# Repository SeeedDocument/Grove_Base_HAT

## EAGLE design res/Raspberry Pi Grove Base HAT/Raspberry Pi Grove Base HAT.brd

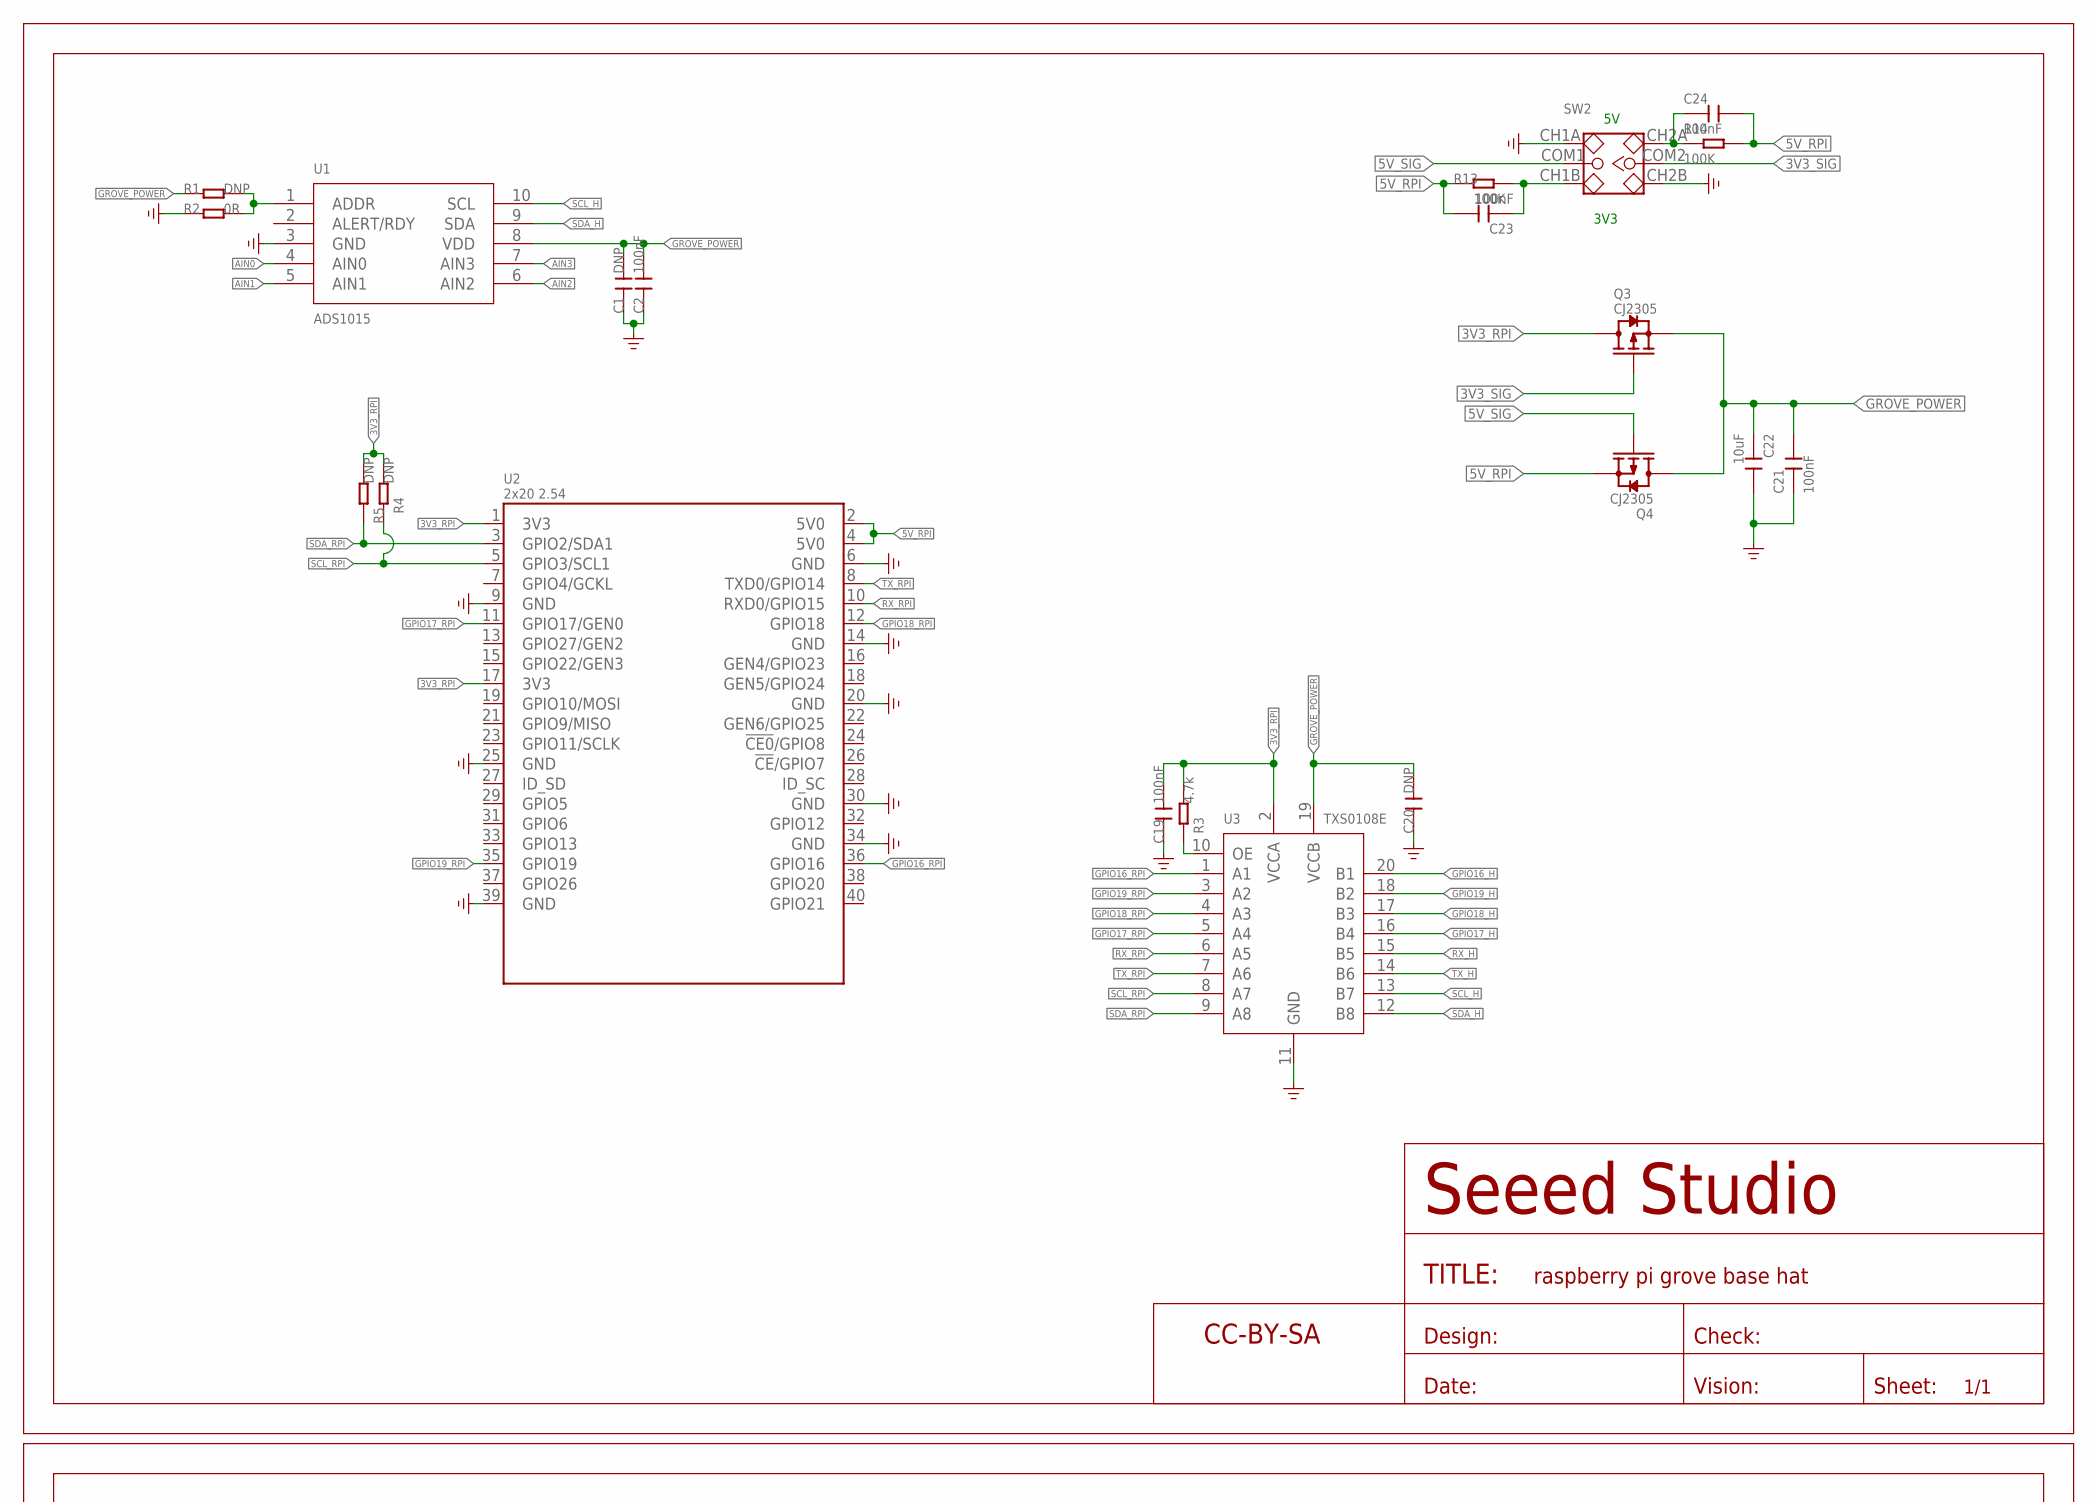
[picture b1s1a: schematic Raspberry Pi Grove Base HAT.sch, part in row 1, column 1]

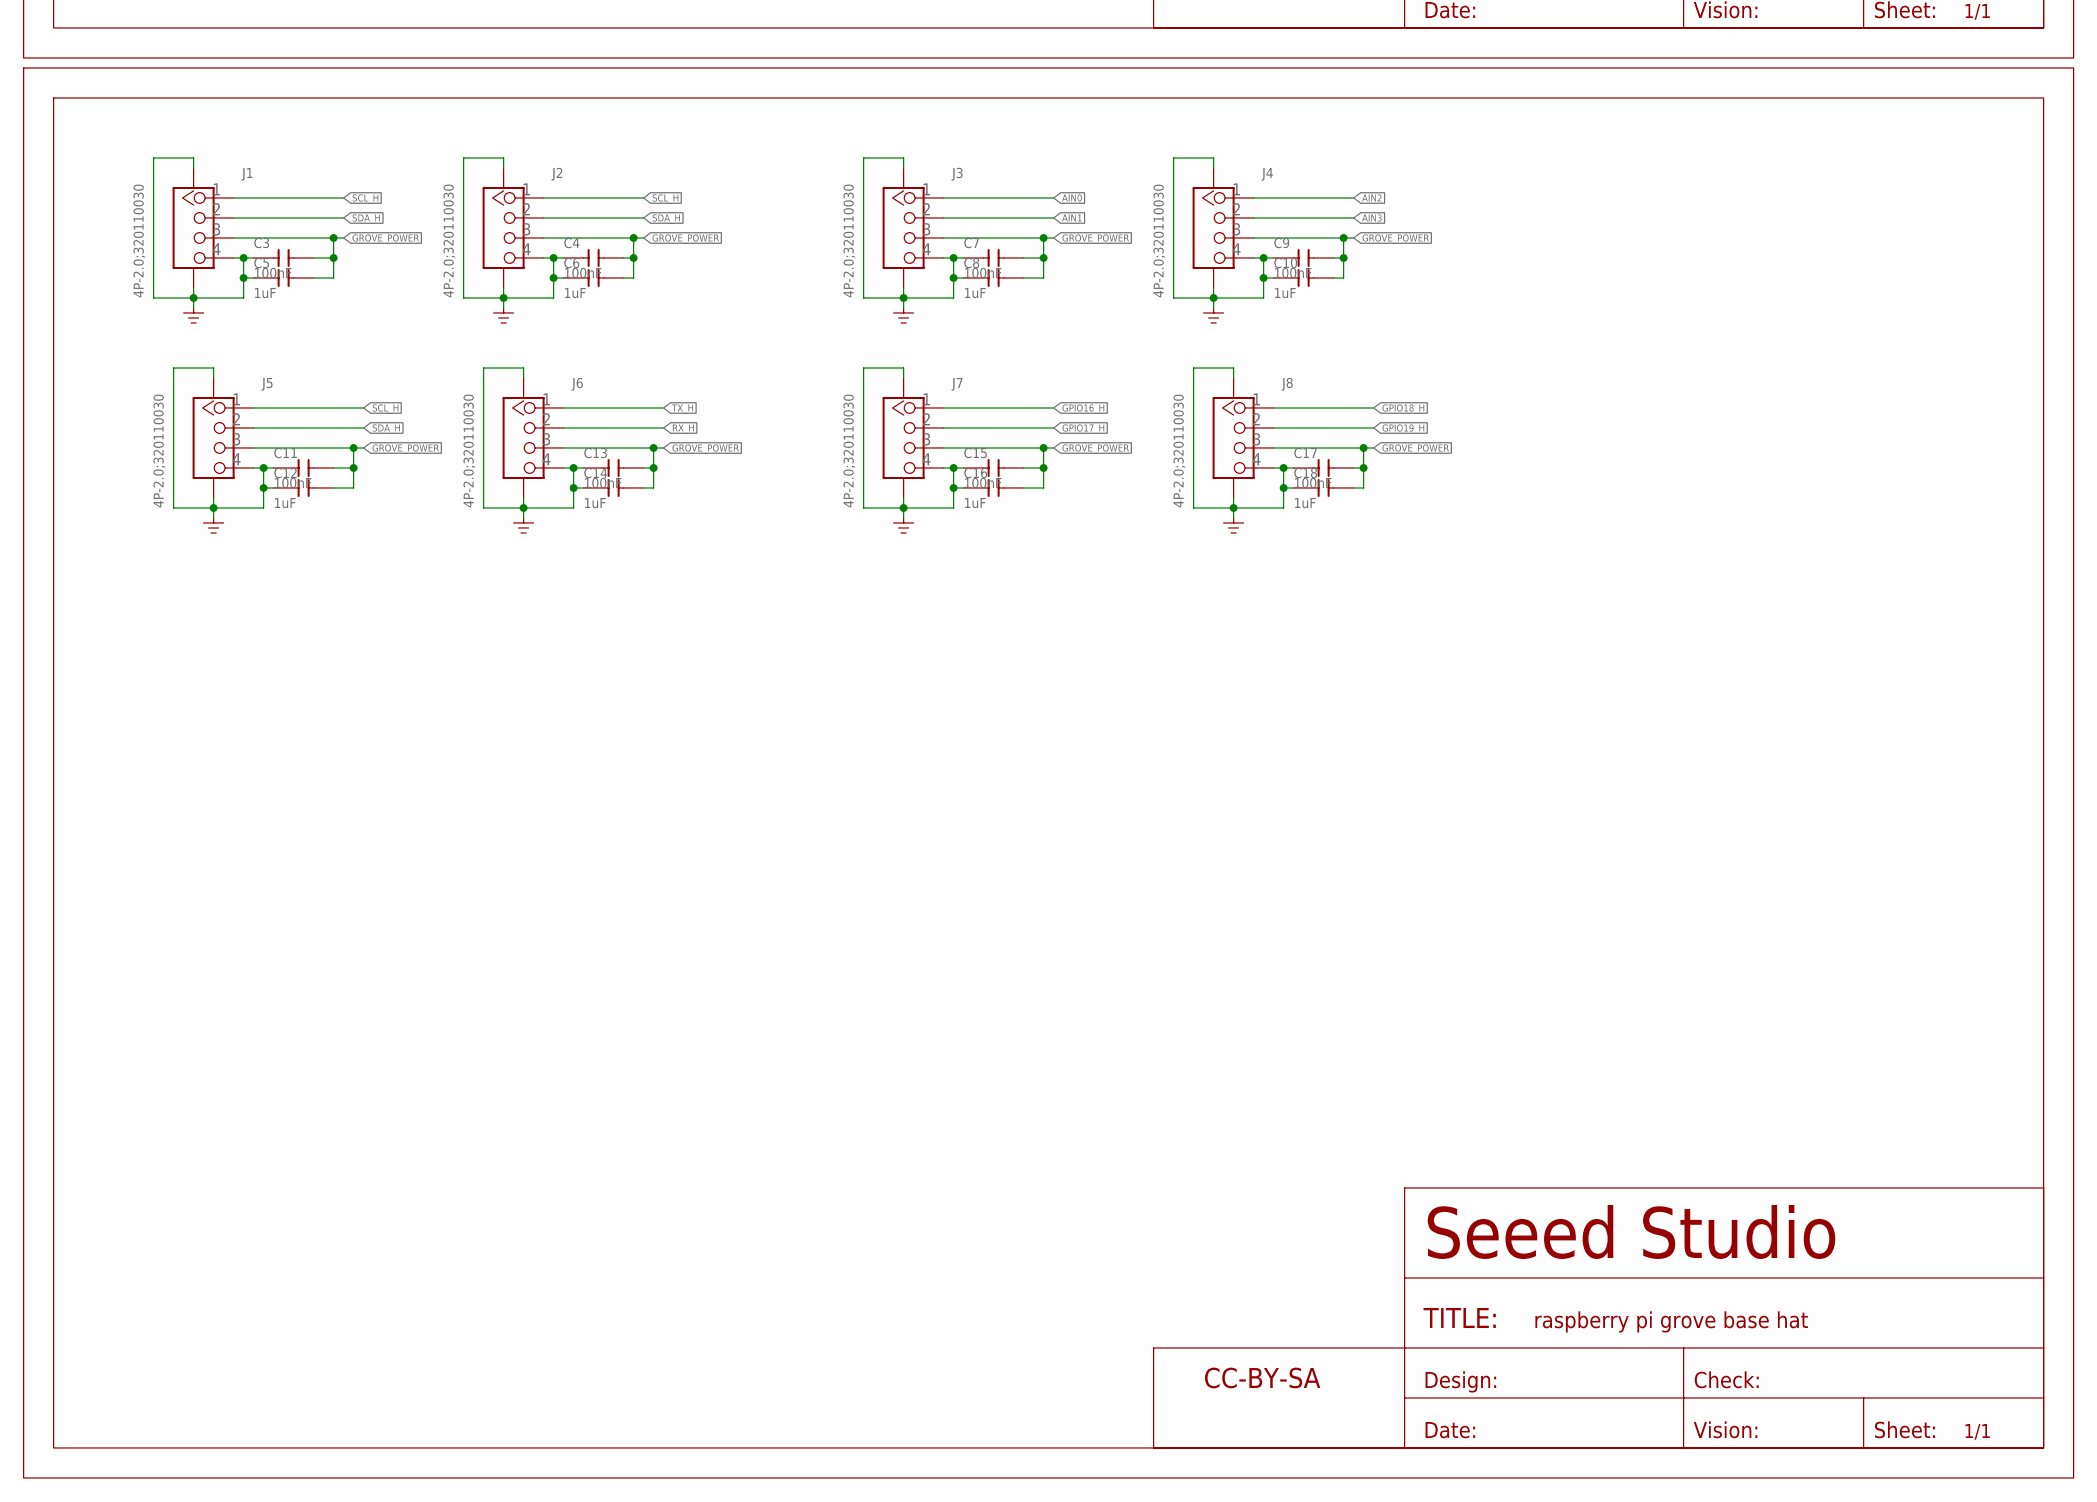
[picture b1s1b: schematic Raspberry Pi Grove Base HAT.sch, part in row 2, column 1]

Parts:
C1, C20: DNP; C0603
C2, C3, C4, C7, C9, C11, C13, C15, C17, C19, C21, C23, C24: 100nF; C0603
C5, C6, C8, C10, C12, C14, C16, C18: 1uF; C0603
C22: 10uF; C0603
FR, FR1: SEEEDSTUDIO-OPEN-SCH-FRAME; SEEEDSTUDIO-PCB-FRAME
J1, J2, J3, J4, J5, J6: 4P-2.0;320110030; HW4-SMD-2.0
J7, J8: 4P-2.0;320110030; HW4-SMD-2.0-90D
Q3, Q4: CJ2305; SOT-23
R1, R4, R5: DNP; R0603
R2: 0R; R0603
R3: 4.7k; R0603
R13, R14: 100K; R0603
SW2: SWITCH-2CH-6P-2.54; 6P-SMD-2CH-2.54-3.5X7.2
U1: ADS1015; SSOP10-0.5-3X3MM
U2: 2x20 2.54; RASPI_BOARD_B+HAT_DF_CF
U3: TXS0108E; TSSOP20-0.65-6.5X4.4MM

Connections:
3V3_RPI: C19.2, Q3.3 (D), R3.2, R4.2, R5.2, U2.1 (3V3), U2.17 (3V3), U3.2 (VCCA)
3V3_SIG: Q3.1 (G), SW2.COM2
5V_RPI: C23.2, C24.2, Q4.2 (S), R13.1, R14.2, U2.2 (5V0), U2.4 (5V0)
5V_SIG: Q4.1 (G), SW2.COM1
AIN0: J3.1, U1.4 (AIN0)
AIN1: J3.2, U1.5 (AIN1)
AIN2: J4.1, U1.6 (AIN2)
AIN3: J4.2, U1.7 (AIN3)
GND: C1.1, C2.1, C3.1, C4.1, C5.1, C6.1, C7.1, C8.1, C9.1, C10.1, C11.1, C12.1, C13.1, C14.1, C15.1, C16.1, C17.1, C18.1, C19.1, C20.1, C21.1, C22.2, J1.4, J1.SS1, J1.SS2, J2.4, J2.SS1, J2.SS2, J3.4, J3.SS1, J3.SS2, J4.4, J4.SS1, J4.SS2, J5.4, J5.SS1, J5.SS2, J6.4, J6.SS1, J6.SS2, J7.4, J7.SS1, J7.SS2, J8.4, J8.SS1, J8.SS2, R2.1, SW2.CH1A, SW2.CH2B, U1.3 (GND), U2.6 (GND), U2.9 (GND), U2.14 (GND), U2.20 (GND), U2.25 (GND), U2.30 (GND), U2.34 (GND), U2.39 (GND), U3.11 (GND)
GPIO16_H: J7.1, U3.20 (B1)
GPIO16_RPI: U2.36 (GPIO16), U3.1 (A1)
GPIO17_H: J7.2, U3.16 (B4)
GPIO17_RPI: U2.11 (GPIO17/GEN0), U3.5 (A4)
GPIO18_H: J8.1, U3.17 (B3)
GPIO18_RPI: U2.12 (GPIO18), U3.4 (A3)
GPIO19_H: J8.2, U3.18 (B2)
GPIO19_RPI: U2.35 (GPIO19), U3.3 (A2)
GROVE_POWER: C1.2, C2.2, C3.2, C4.2, C5.2, C6.2, C7.2, C8.2, C9.2, C10.2, C11.2, C12.2, C13.2, C14.2, C15.2, C16.2, C17.2, C18.2, C20.2, C21.2, C22.1, J1.3, J2.3, J3.3, J4.3, J5.3, J6.3, J7.3, J8.3, Q3.2 (S), Q4.3 (D), R1.1, U1.8 (VDD), U3.19 (VCCB)
unnamed: R1.2, R2.2, U1.1 (ADDR)
unnamed: R3.1, U3.10 (OE)
unnamed: C23.1, R13.2, SW2.CH1B
unnamed: C24.1, R14.1, SW2.CH2A
RX_H: J6.2, U3.15 (B5)
RX_RPI: U2.10 (RXD0/GPIO15), U3.6 (A5)
SCL_H: J1.1, J2.1, J5.1, U1.10 (SCL), U3.13 (B7)
SCL_RPI: R4.1, U2.5 (GPIO3/SCL1), U3.8 (A7)
SDA_H: J1.2, J2.2, J5.2, U1.9 (SDA), U3.12 (B8)
SDA_RPI: R5.1, U2.3 (GPIO2/SDA1), U3.9 (A8)
TX_H: J6.1, U3.14 (B6)
TX_RPI: U2.8 (TXD0/GPIO14), U3.7 (A6)

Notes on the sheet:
3V3

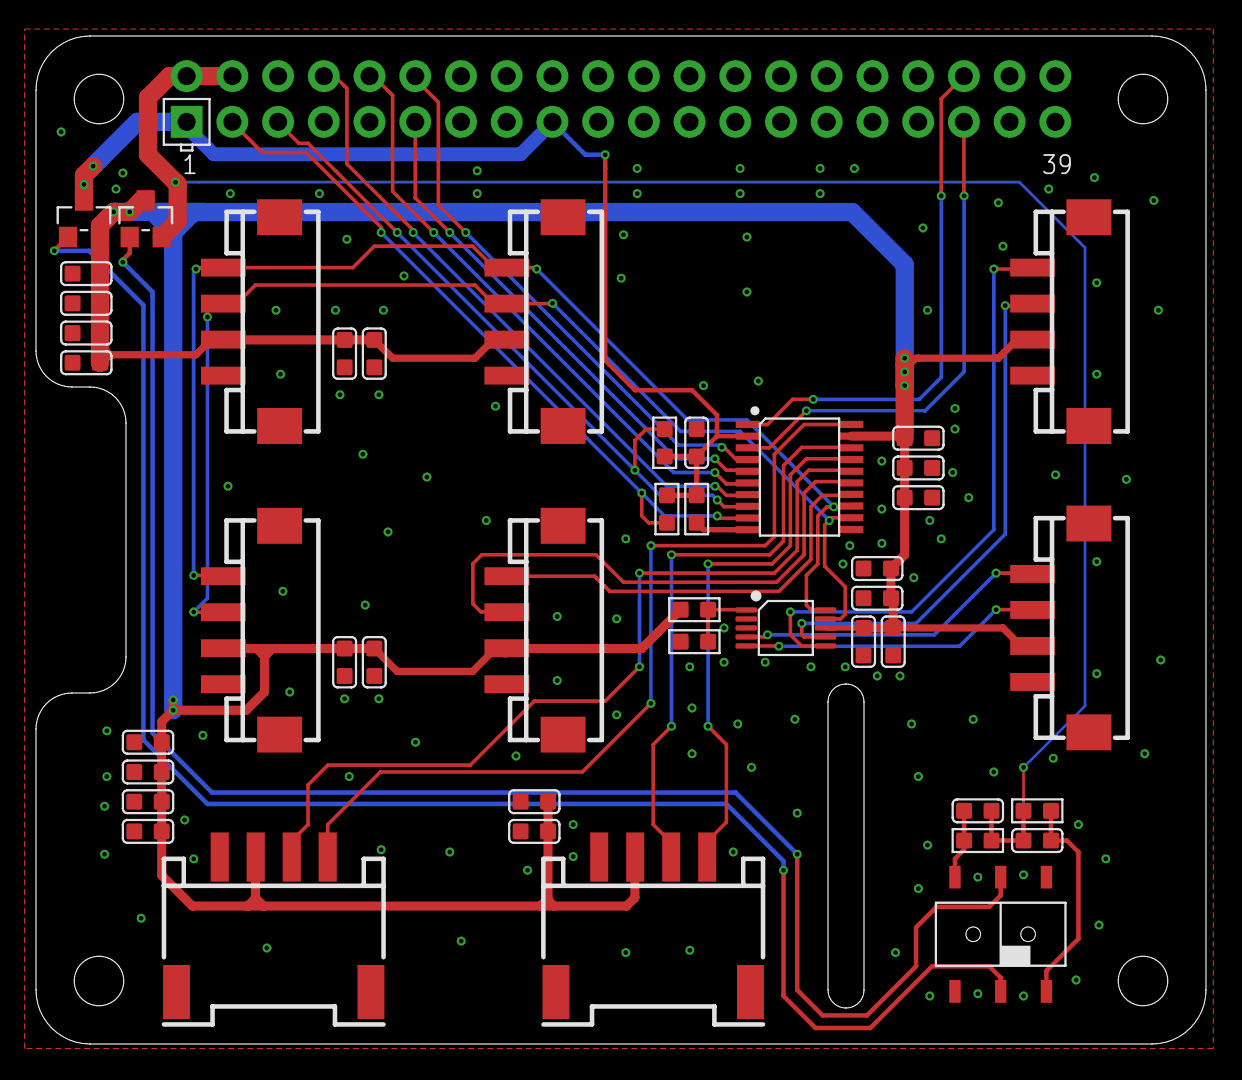
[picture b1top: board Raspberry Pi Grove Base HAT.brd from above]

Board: 2 copper layers, 65.0 x 56.0 mm, 47 parts (0 on the bottom side), 30 nets.

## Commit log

2019-11-01 add
    add

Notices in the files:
parts and their libraries:
moudle-new: This work is licensed under the Creative Commons Attribution 4.0 International License.
To view a copy of this license,visit:
http://creativecommons.org/licenses/by-sa/4.0
moudle-new: CC-BY-SA
